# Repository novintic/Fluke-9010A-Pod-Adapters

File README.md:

# Fluke-9010A-Pod-Adapters

Some quality of life improvements for Fluke 9010A Reproduction Pod users:

Fluke Pod adapter: use a standard DB 25 cable with your repro pod. Should work with the 'small' pods like Z80 and 6502. For Z80 you will need to use a low footprint crystal for the adapter to fit.

Fluke Pod adapter large: use a standard DB 25 cable with your repro pod. Should work with the 'large' pods like 6809 and 68000.

Z80 and 6502 Pod 2x40 Pin Cable: Use a double 40pin ribbon cable to get better signal quality / more stable interfacing even with longer cables.

If you don't know what all this means, you probably won't need any of it..;)

Have fun

01/2025
Added 6502 2x40 pin cable

07/2024
Uploaded files for 6809 and 68K pod-to-UUT cable headers too.

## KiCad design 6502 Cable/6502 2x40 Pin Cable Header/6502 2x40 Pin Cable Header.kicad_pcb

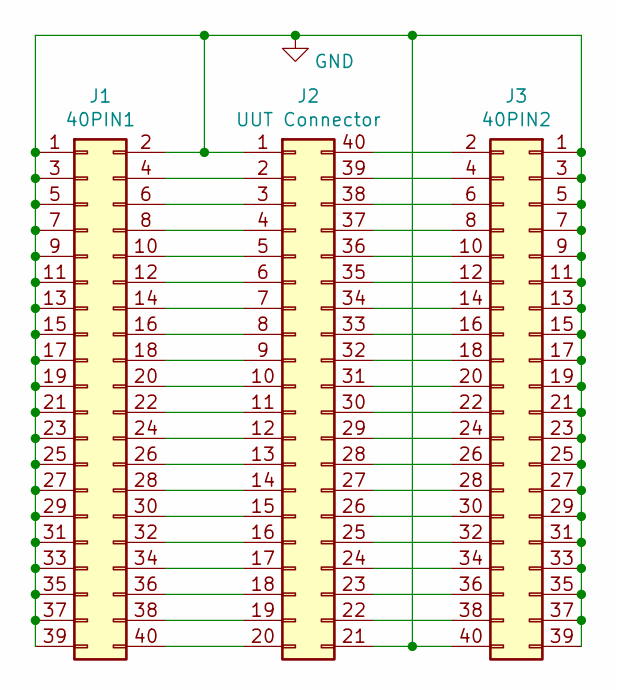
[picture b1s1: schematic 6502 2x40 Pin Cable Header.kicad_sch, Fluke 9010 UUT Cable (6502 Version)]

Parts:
J1: 40PIN1; PinSocket_2x20_P2.54mm_Vertical
J2: UUT Connector; DIP-40_W15.24mm
J3: 40PIN2; PinSocket_2x20_P2.54mm_Vertical

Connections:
GND: J1.1, J1.2, J1.3, J1.5, J1.7, J1.9, J1.11, J1.13, J1.15, J1.17, J1.19, J1.21, J1.23, J1.25, J1.27, J1.29, J1.31, J1.33, J1.35, J1.37, J1.39, J2.1, J2.21, J3.1, J3.3, J3.5, J3.7, J3.9, J3.11, J3.13, J3.15, J3.17, J3.19, J3.21, J3.23, J3.25, J3.27, J3.29, J3.31, J3.33, J3.35, J3.37, J3.39, J3.40
unnamed: J1.4, J2.2
unnamed: J1.6, J2.3
unnamed: J1.8, J2.4
unnamed: J1.10, J2.5
unnamed: J1.12, J2.6
unnamed: J1.14, J2.7
unnamed: J1.16, J2.8
unnamed: J1.18, J2.9
unnamed: J1.20, J2.10
unnamed: J1.22, J2.11
unnamed: J1.24, J2.12
unnamed: J1.26, J2.13
unnamed: J1.28, J2.14
unnamed: J1.30, J2.15
unnamed: J1.32, J2.16
unnamed: J1.34, J2.17
unnamed: J1.36, J2.18
unnamed: J1.38, J2.19
unnamed: J1.40, J2.20
unnamed: J2.22, J3.38
unnamed: J2.23, J3.36
unnamed: J2.24, J3.34
unnamed: J2.25, J3.32
unnamed: J2.26, J3.30
unnamed: J2.27, J3.28
unnamed: J2.28, J3.26
unnamed: J2.29, J3.24
unnamed: J2.30, J3.22
unnamed: J2.31, J3.20
unnamed: J2.32, J3.18
unnamed: J2.33, J3.16
unnamed: J2.34, J3.14
unnamed: J2.35, J3.12
unnamed: J2.36, J3.10
unnamed: J2.37, J3.8
unnamed: J2.38, J3.6
unnamed: J2.39, J3.4
unnamed: J2.40, J3.2

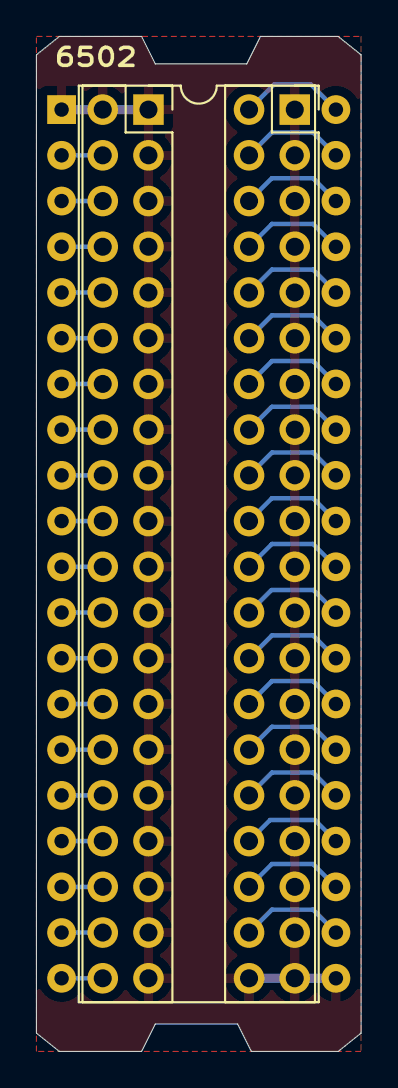
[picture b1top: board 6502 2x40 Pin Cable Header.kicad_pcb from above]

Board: 2 copper layers, 18.0 x 56.4 mm, 3 parts (0 on the bottom side), 39 nets.

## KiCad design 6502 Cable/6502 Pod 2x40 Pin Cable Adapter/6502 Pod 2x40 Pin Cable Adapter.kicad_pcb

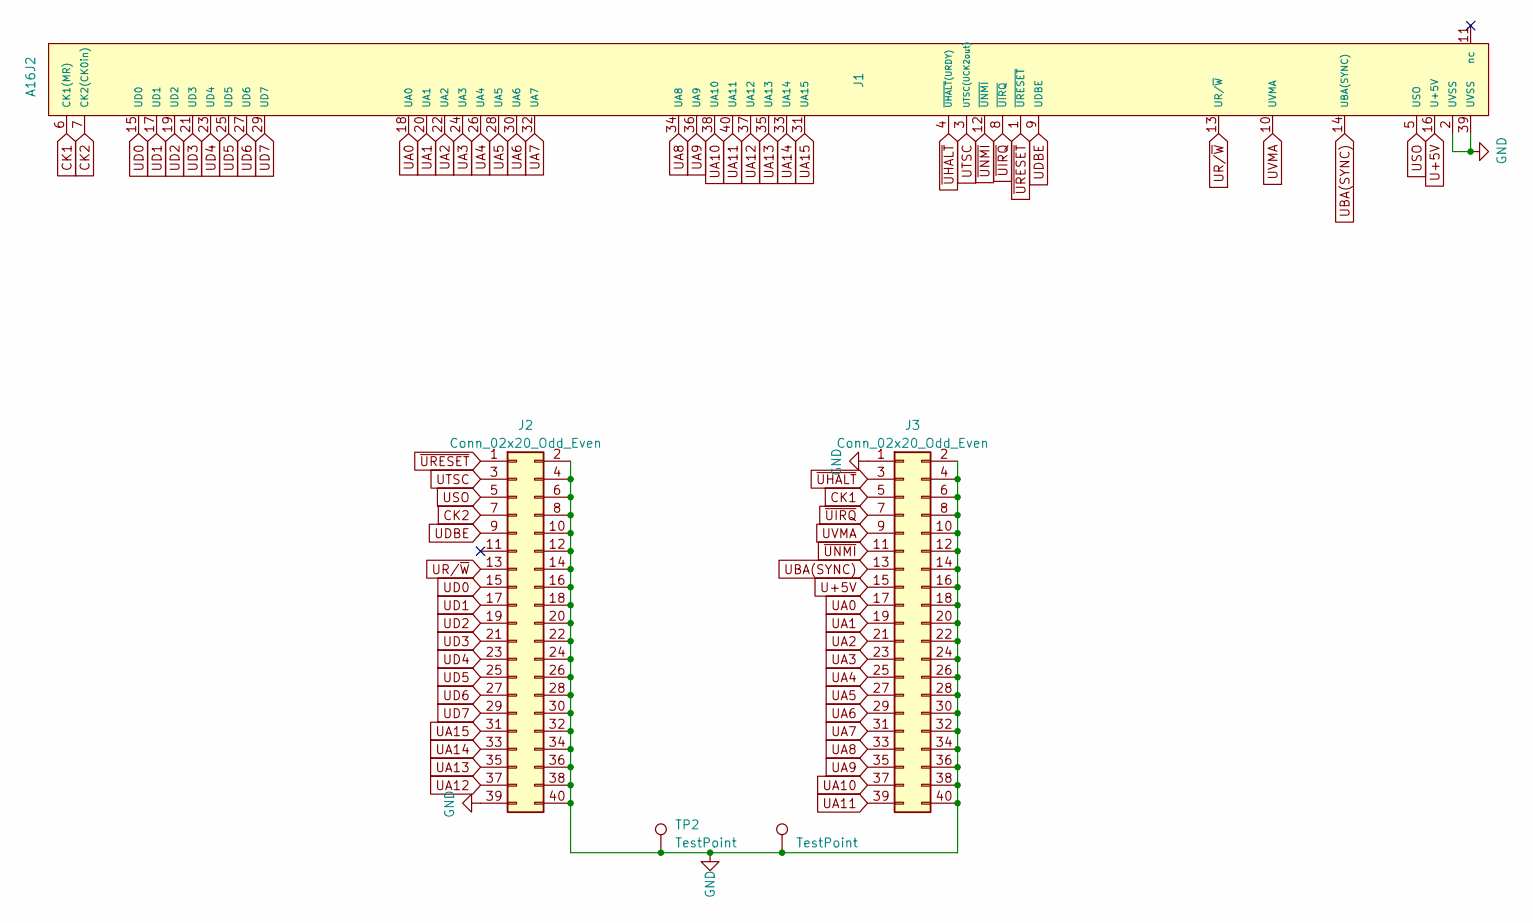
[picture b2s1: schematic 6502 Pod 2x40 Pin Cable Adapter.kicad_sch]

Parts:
J1: A16J2; PinHeader_2x20_P2.54mm_Vertical
J2, J3: Conn_02x20_Odd_Even; PinHeader_2x20_P2.54mm_Vertical
TP1, TP2: TestPoint; PinHeader_1x01_P1.00mm_Vertical

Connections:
CK1: J1.6 (CK1(MR)), J3.5
CK2: J1.7 (CK2(CK0in)), J2.7
GND: J1.2 (UVSS), J1.39 (UVSS), J2.2, J2.4, J2.6, J2.8, J2.10, J2.12, J2.14, J2.16, J2.18, J2.20, J2.22, J2.24, J2.26, J2.28, J2.30, J2.32, J2.34, J2.36, J2.38, J2.39, J2.40, J3.1, J3.2, J3.4, J3.6, J3.8, J3.10, J3.12, J3.14, J3.16, J3.18, J3.20, J3.22, J3.24, J3.26, J3.28, J3.30, J3.32, J3.34, J3.36, J3.38, J3.40, TP1.1, TP2.1
U+5V: J1.16 (U+5V), J3.15
UA0: J1.18 (UA0), J3.17
UA1: J1.20 (UA1), J3.19
UA2: J1.22 (UA2), J3.21
UA3: J1.24 (UA3), J3.23
UA4: J1.26 (UA4), J3.25
UA5: J1.28 (UA5), J3.27
UA6: J1.30 (UA6), J3.29
UA7: J1.32 (UA7), J3.31
UA8: J1.34 (UA8), J3.33
UA9: J1.36 (UA9), J3.35
UA10: J1.38 (UA10), J3.37
UA11: J1.40 (UA11), J3.39
UA12: J1.37 (UA12), J2.37
UA13: J1.35 (UA13), J2.35
UA14: J1.33 (UA14), J2.33
UA15: J1.31 (UA15), J2.31
UBA(SYNC): J1.14 (UBA(SYNC)), J3.13
UD0: J1.15 (UD0), J2.15
UD1: J1.17 (UD1), J2.17
UD2: J1.19 (UD2), J2.19
UD3: J1.21 (UD3), J2.21
UD4: J1.23 (UD4), J2.23
UD5: J1.25 (UD5), J2.25
UD6: J1.27 (UD6), J2.27
UD7: J1.29 (UD7), J2.29
UDBE: J1.9 (UDBE), J2.9
UR/~W: J1.13 (UR/~W), J2.13
USO: J1.5 (USO), J2.5
UTSC: J1.3 (UTSC(UCK2out)), J2.3
UVMA: J1.10 (UVMA), J3.9
~UHALT: J1.4 (~UHALT(URDY)), J3.3
~UIRQ: J1.8 (~UIRQ), J3.7
~UNMI: J1.12 (~UNMI), J3.11
~URESET: J1.1 (~URESET), J2.1

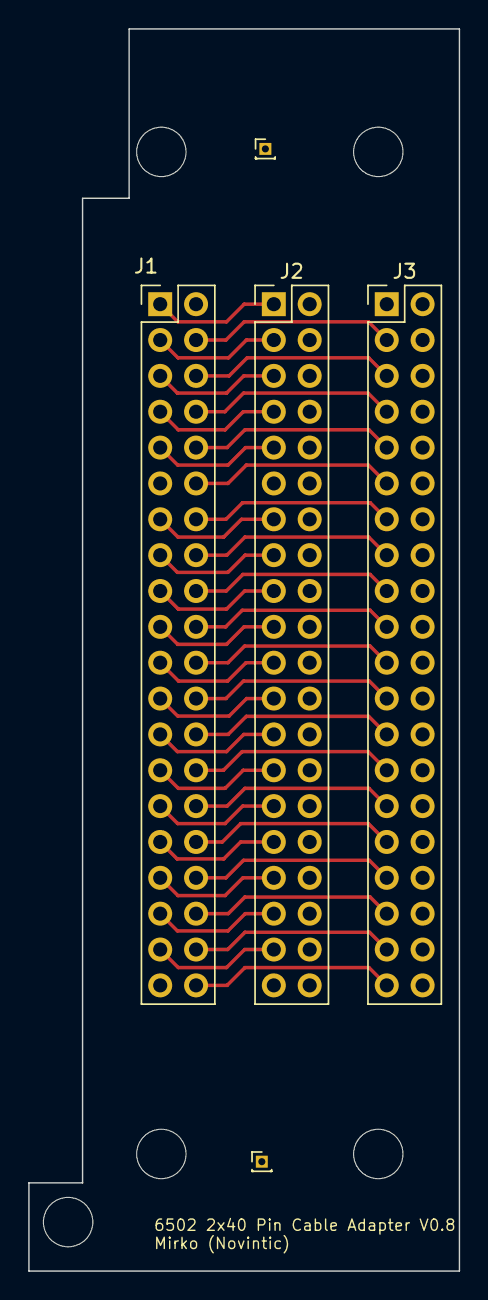
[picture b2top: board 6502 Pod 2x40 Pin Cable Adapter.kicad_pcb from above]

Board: 2 copper layers, 30.5 x 88.0 mm, 5 parts (0 on the bottom side), 38 nets.

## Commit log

2024-07-13 Add files via upload
    Header PCB for 6809(E) Pod-to-UUT cable
2024-07-13 Add files via upload
    Header PCB for 68K pod-to-UUT cable
